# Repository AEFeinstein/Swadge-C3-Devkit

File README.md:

# Swadge-C3-Devkit

It's a Swadge devkit featuring:

* [ESP32-C3-MINI-1](https://www.espressif.com/sites/default/files/documentation/esp32-c3-mini-1_datasheet_en.pdf)
* [QMA6981 Accelerometer](https://datasheet.lcsc.com/szlcsc/QST-QMA6981_C310611.pdf)
* [0.96" 128x64 OLED Display](https://www.buydisplay.com/download/manual/ER-OLED0.96-1_Series_Datasheet.pdf)
* [Microphone](https://www.puiaudio.com/media/SpecSheet/POM-2738P-R.pdf)
* [Piezo Buzzer](https://datasheet.lcsc.com/szlcsc/1808301434_ZLFY-ZL-YDW1207-4005PA-5-0_C219727.pdf)
* 8x [WS2812b LEDs](https://cdn-shop.adafruit.com/datasheets/WS2812B.pdf)
* 8x [Tactile buttons](https://www.te.com/commerce/DocumentDelivery/DDEController?Action=srchrtrv&DocNm=2-1437565-7&DocType=Customer+Drawing&DocLang=Englishe)
* 2x [AA Battery clips](http://www.keyelco.com/product-pdf.cfm?p=1025)
* [Micro USB Power](https://www.molex.com/pdm_docs/sd/473460001_sd.pdf)

It's compatible with the [Swadge Programmer](https://github.com/AEFeinstein/Super-2020-Swadge-HW/tree/master/hardware/swadge-programmer) used for ESP8266 based Swadges, though some GPIOs aren't broken out on the v2 programmer.

# 3D Render

# Schematic

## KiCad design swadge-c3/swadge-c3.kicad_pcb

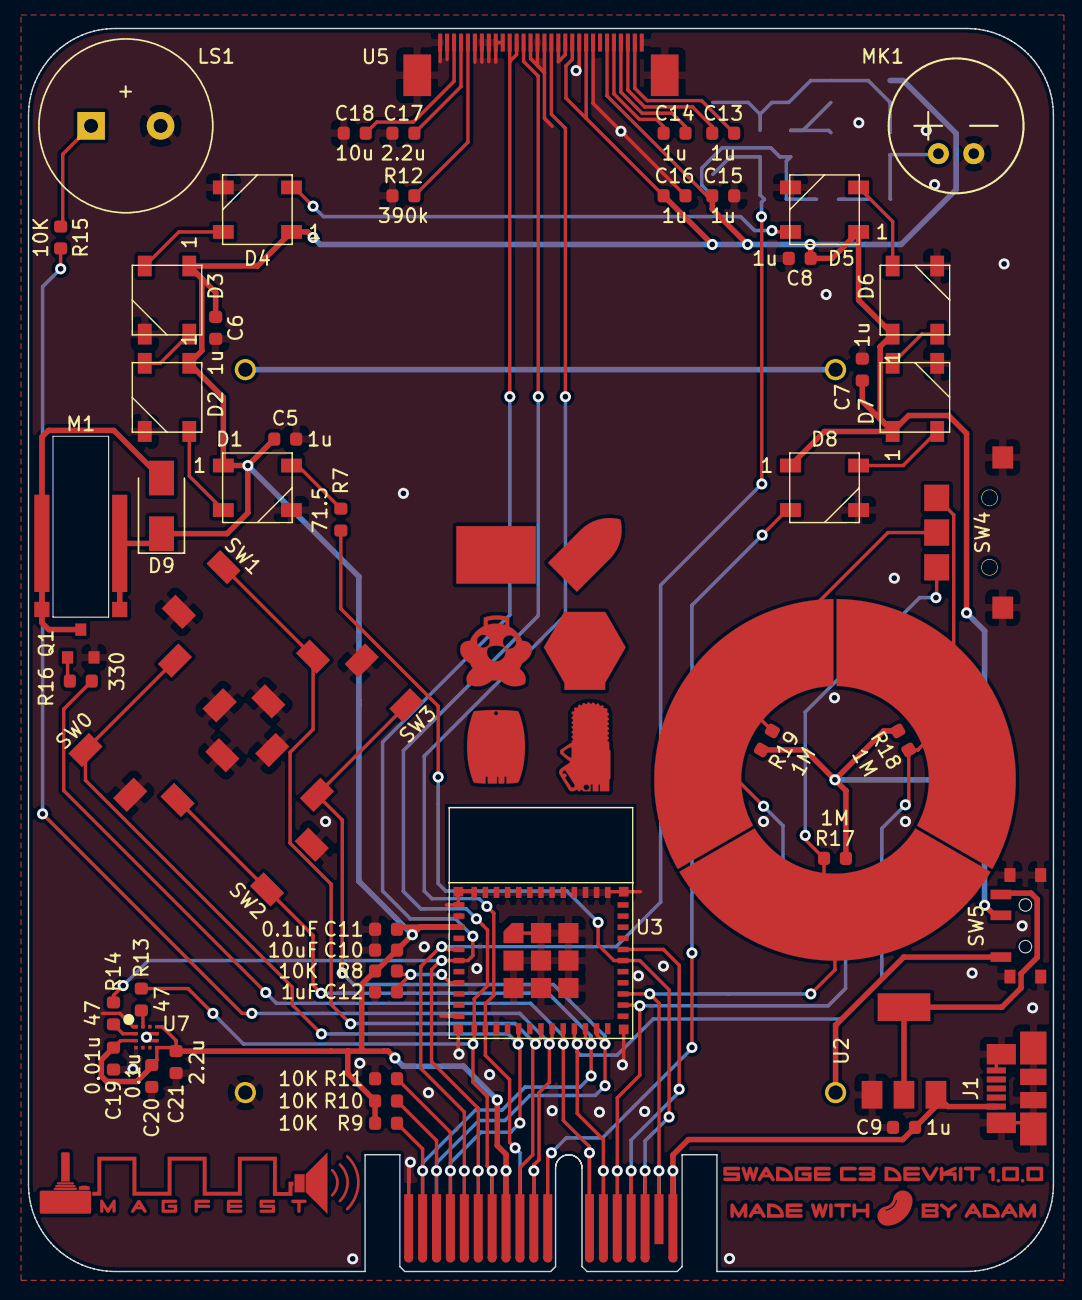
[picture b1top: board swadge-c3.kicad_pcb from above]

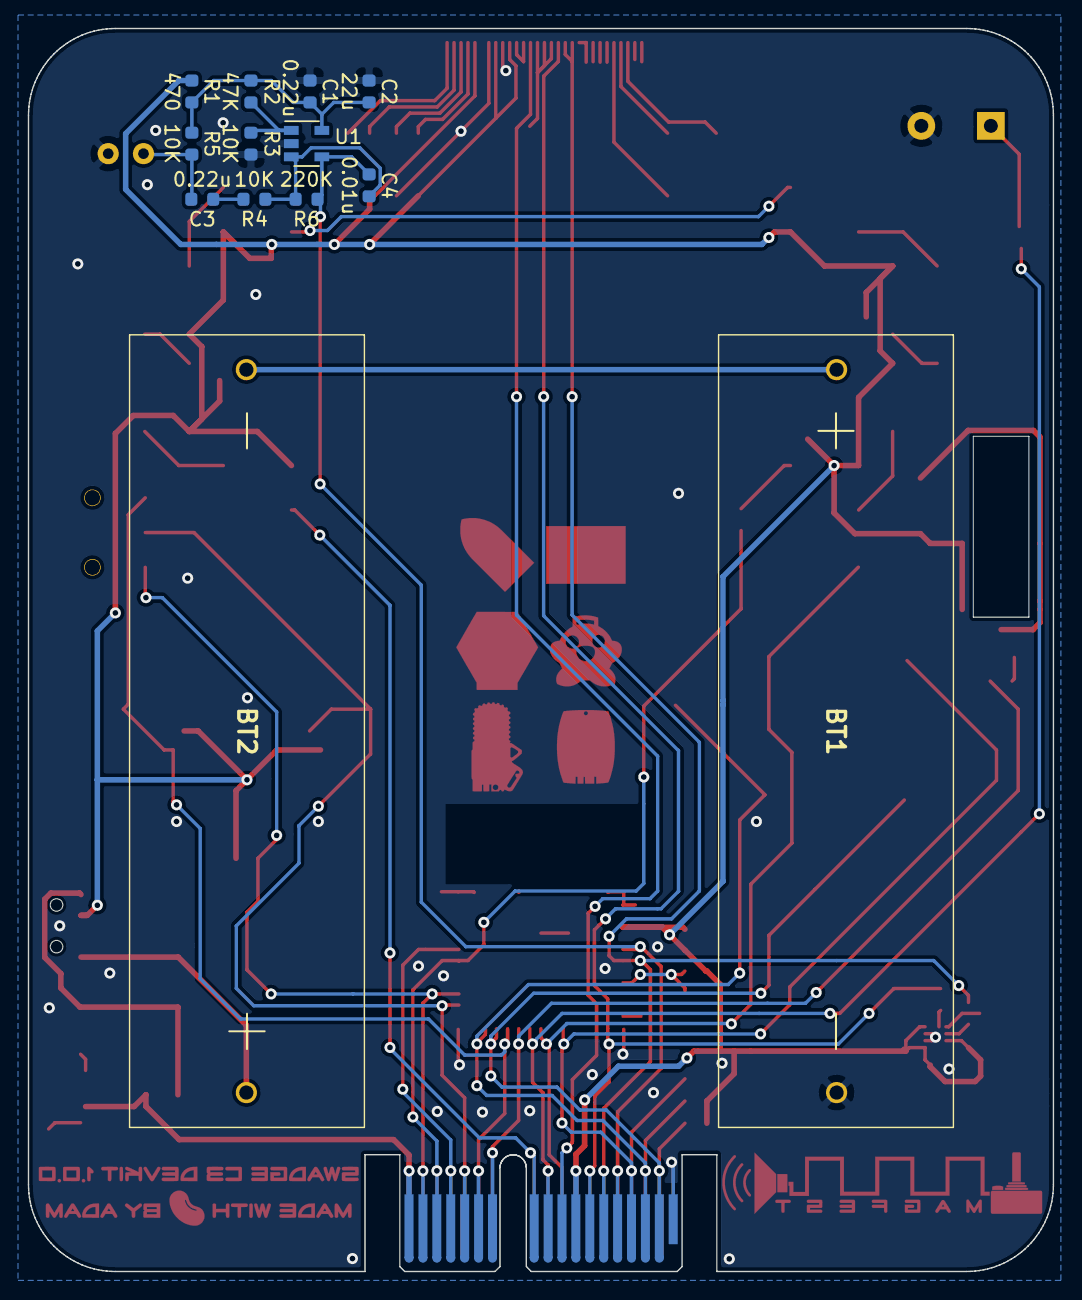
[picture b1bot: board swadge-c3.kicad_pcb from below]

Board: 2 copper layers, 73.7 x 89.4 mm, 73 parts (13 on the bottom side), 48 nets.

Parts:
BT1, BT2: Battery; 2460
C1, C3: 0.22u; C_0603_1608Metric
C2: 22u; C_0603_1608Metric
C4, C19: 0.01u; C_0603_1608Metric
C5, C6, C7, C8, C9, C13, C14, C15, C16: 1u; C_0603_1608Metric
C10: 10uF; C_0603_1608Metric
C11: 0.1uF; C_0603_1608Metric
C12: 1uF; C_0603_1608Metric
C17, C21: 2.2u; C_0603_1608Metric
C18: 10u; C_0603_1608Metric
C20: 0.1u; C_0603_1608Metric
D1, D2, D3, D4, D5, D6, D7, D8: WS2812B; LED_WS2812B_PLCC4_5.0x5.0mm_P3.2mm
D9: D; D_SMA
J1: USB_B_Micro; USB_Micro-B_Molex_47346-0001
LS1: Speaker; Buzzer_12.5x7.5
M1: Motor_DC; Z30C1B839982L
MK1: Microphone; CMA-4544PF-W
Q1: Q_NPN_BEC; SOT-23
R1: 470; R_0603_1608Metric
R2: 47K; R_0603_1608Metric
R3, R4, R5, R8, R9, R10, R11, R15: 10K; R_0603_1608Metric
R6: 220K; R_0603_1608Metric
R7: 71.5; R_0603_1608Metric
R12: 390k; R_0603_1608Metric
R13, R14: 47; R_0603_1608Metric
R16: 330; R_0603_1608Metric
R17, R18, R19: 1M; R_0603_1608Metric
SW0, SW1, SW2, SW3: 4-1437565-2; SW_4-1437565-2
SW4: LEVER8184
SW5: SW_SPDT; SW_SPDT_PCM12
TC1: touch-ring-3
U1: GS321-TR; SOT-23-5
U2: AP1117-33; SOT-223-3_TabPin2
U3: ESP32-C3-MINI-1; esp32-c2-mini-1
U4: BUS_PCIexpress
U5: OLED_CONNECTOR; ER-OLED0.96-1.3
U6: OLED_DISPLAY; NULL
U7: QMA7981; QMA6981
U8: art_made_by_adam; made-by-adam
U9: art_mag_logo_metal; mag-logo-metal
U10: art_swadge_family; swadges-family

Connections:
+3V3: C5.1, C6.1, C7.1, C8.1, C10.1, C11.1, C15.2, C16.2, C19.2, C20.2, C21.2, D1.1, D2.1, D3.1, D4.1, D5.1, D6.1, D7.1, D8.1, D9.1, M1.1, R1.1, R8.2, R9.1, R10.1, R17.2, R18.2, R19.2, SW5.2, U3.3, U4.A8, U4.B8, U5.6, U5.9, U5.11, U7.3, U7.7, U7.10
+5V: C9.2, J1.1, U2.3, U4.A18, U4.B18
EN: C12.1, R8.1, U3.8
GND: BT1.2, C1.1, C2.1, C5.2, C6.2, C7.2, C8.2, C9.1, C10.2, C11.2, C12.2, C15.1, C16.1, C17.1, C18.1, C19.1, C20.1, C21.1, D1.3, D2.3, D3.3, D4.3, D5.3, D6.3, D7.3, D8.3, J1.5, J1.6, LS1.2, MK1.1, Q1.2, R3.1, R11.1, R12.1, SW0.3, SW0.4, SW1.3, SW1.4, SW2.3, SW2.4, SW3.3, SW3.4, SW4.C, SW5.4, SW5.5, SW5.6, SW5.7, U1.2, U2.1, U3.1, U3.2, U3.11, U3.14, U3.36, U3.37, U3.38, U3.39, U3.40, U3.41, U3.42, U3.43, U3.44, U3.45, U3.46, U3.47, U3.48, U3.49, U3.50, U3.51, U3.52, U3.53, U3.54, U3.55, U3.56, U3.57, U3.58, U3.59, U3.60, U3.61, U4.A1, U4.B1, U5.1, U5.8, U5.10, U5.12, U5.13, U5.15, U5.16, U5.17, U5.21, U5.22, U5.23, U5.24, U5.25, U5.29, U5.30, U5.31, U7.1, U7.4, U7.8, U7.9
IO0_SCL: R13.2, U3.12, U4.A7, U4.B7, U5.18
IO1_RES: U3.13, U4.A9, U5.14
IO2_MIC: C4.1, R6.1, U1.4, U3.5, U4.A5, U4.B5
IO3_SDA: R14.2, U3.6, U4.A6, U4.B6, U5.19, U5.20
IO4_SW1: SW1.1, SW1.2, U3.18, U4.B9
IO5_BZR: R15.2, U3.19, U4.A10, U4.B10
IO6_VIB: R16.2, U3.20, U4.A12, U4.B12
IO7_TC0: R18.1, SW4.1, TC1.2, U3.21, U4.A13, U4.B13
IO8_SW2: R9.2, SW2.1, SW2.2, U3.22, U4.A2, U4.B2
IO9_SW3: R10.2, SW3.1, SW3.2, U3.23, U4.A3, U4.B3
IO10_SW0: R11.2, SW0.1, SW0.2, U3.16, U4.A4, U4.B4
IO18_TC1: R19.1, SW4.T, TC1.1, U3.26, U4.A14, U4.B14
IO19_TC2: R17.1, SW4.2, TC1.3, U3.27, U4.A17, U4.B17
LED_OUT: D8.2, U4.A11, U4.B11
unnamed: BT1.1, BT2.2
unnamed: BT2.1, SW5.1
unnamed: C1.2, C2.2, R1.2, R2.2, R5.1, U1.5
unnamed: C3.1, R4.2
unnamed: C3.2, MK1.2, R5.2
unnamed: C4.2, R4.1, R6.2, U1.3
unnamed: C13.1, U5.2
unnamed: C13.2, U5.3
unnamed: C14.1, U5.4
unnamed: C14.2, U5.5
unnamed: C17.2, U5.27
unnamed: C18.2, U5.28
unnamed: D1.2, D2.4
unnamed: D1.4, R7.1
unnamed: D2.2, D3.4
unnamed: D3.2, D4.4
unnamed: D4.2, D5.4
unnamed: D5.2, D6.4
unnamed: D6.2, D7.4
unnamed: D7.2, D8.4
unnamed: D9.2, M1.2, Q1.3
unnamed: LS1.1, R15.1
unnamed: Q1.1, R16.1
unnamed: R2.1, R3.2, U1.1
unnamed: R12.2, U5.26
unnamed: R13.1, U7.12
unnamed: R14.1, U7.2
unnamed: SW5.3, U2.2
RX: R7.2, U3.30, U4.A16, U4.B16
TX: U3.31, U4.A15, U4.B15

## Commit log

2021-02-26 Added CAD model for ESP32-C3-MINI-1
2021-02-26 Updated schematic
2021-02-27 Edited schematic, started layout
2021-02-27 layout updates
2021-03-01 Update layout
2021-03-01 Complete PCB routing
2021-03-01 Rounded corners
2021-03-01 Fix alignment
2021-03-02 Added art, renders, exported schematic
2021-03-02 Use correct schematic
2021-03-02 Replace SVG schematic with PNG
2021-03-02 Replaced QMA6981 with QMA7981. Updated art. Updated renders
2021-03-02 cleanup
2021-03-07 Added three way thumbswitch
2021-03-22 Replaced four left buttons with scrollwheel
2021-03-22 Added pullups
2021-04-14 Added diode, vib motor, touch ring
2021-04-14 Fixed touch ring, added art
2021-04-14 Update vibration motor CAD
2021-04-14 Added parts for art
2021-04-14 Move around resistors, silk
